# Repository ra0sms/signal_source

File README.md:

## Signal source for tuning receive antennas

More information - https://ra0sms.com/signal-source-for-bog/

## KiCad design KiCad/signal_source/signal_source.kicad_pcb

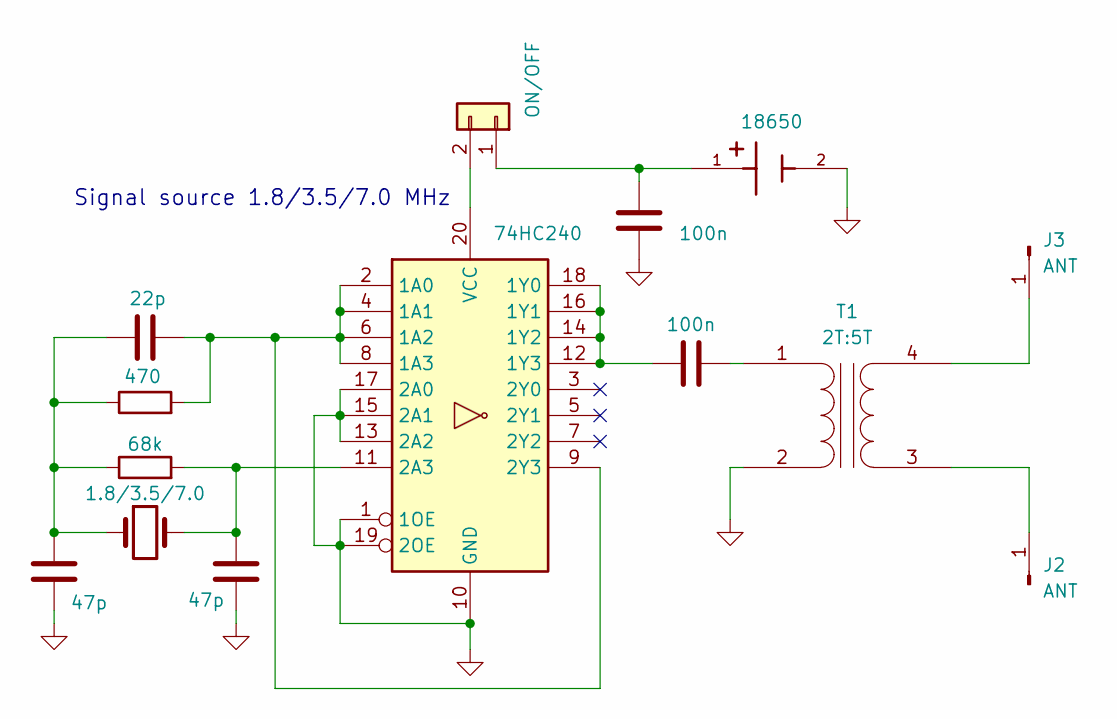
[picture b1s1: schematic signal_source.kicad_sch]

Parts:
BT2: 18650; BAT_BK-18650-PC2; PARTREV F
C1, C2: 100n; C_1206_3216Metric
C3: 22p; C_1206_3216Metric
C4, C5: 47p; C_1206_3216Metric
J1: ON/OFF; PinHeader_1x02_P2.54mm_Vertical
J2, J3: ANT; Banana_Jack_1Pin
R1: 68k; R_1206_3216Metric
R2: 470; R_1206_3216Metric
T1: 2T:5T; Transformer_BN73-202
U1: 74HC240; DIP-20_W7.62mm_Socket_LongPads
Y1: 1.8/3.5/7.0; Crystal_HC49-U_Vertical

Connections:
GND: BT2.2, C2.1, C4.1, C5.1, T1.2 (AB), U1.1 (1OE), U1.10 (GND), U1.13 (2A2), U1.15 (2A1), U1.17 (2A0), U1.19 (2OE); also elsewhere on the board
unnamed: C3.1, C4.2, R1.1, R2.1, Y1.1
unnamed: BT2.1, C2.2, J1.1
unnamed: J1.2, U1.20 (VCC)
unnamed 4: J2.1, T1.3 (SA); also elsewhere on the board
unnamed 5: J3.1, T1.4 (SB); also elsewhere on the board
unnamed 6: C1.2, T1.1 (AA); also elsewhere on the board
unnamed: C3.2, R2.2, U1.2 (1A0), U1.4 (1A1), U1.6 (1A2), U1.8 (1A3), U1.9 (2Y3)
unnamed: C1.1, U1.12 (1Y3), U1.14 (1Y2), U1.16 (1Y1), U1.18 (1Y0)
unnamed: C5.2, R1.2, U1.11 (2A3), Y1.2

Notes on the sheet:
Signal source 1.8/3.5/7.0 MHz

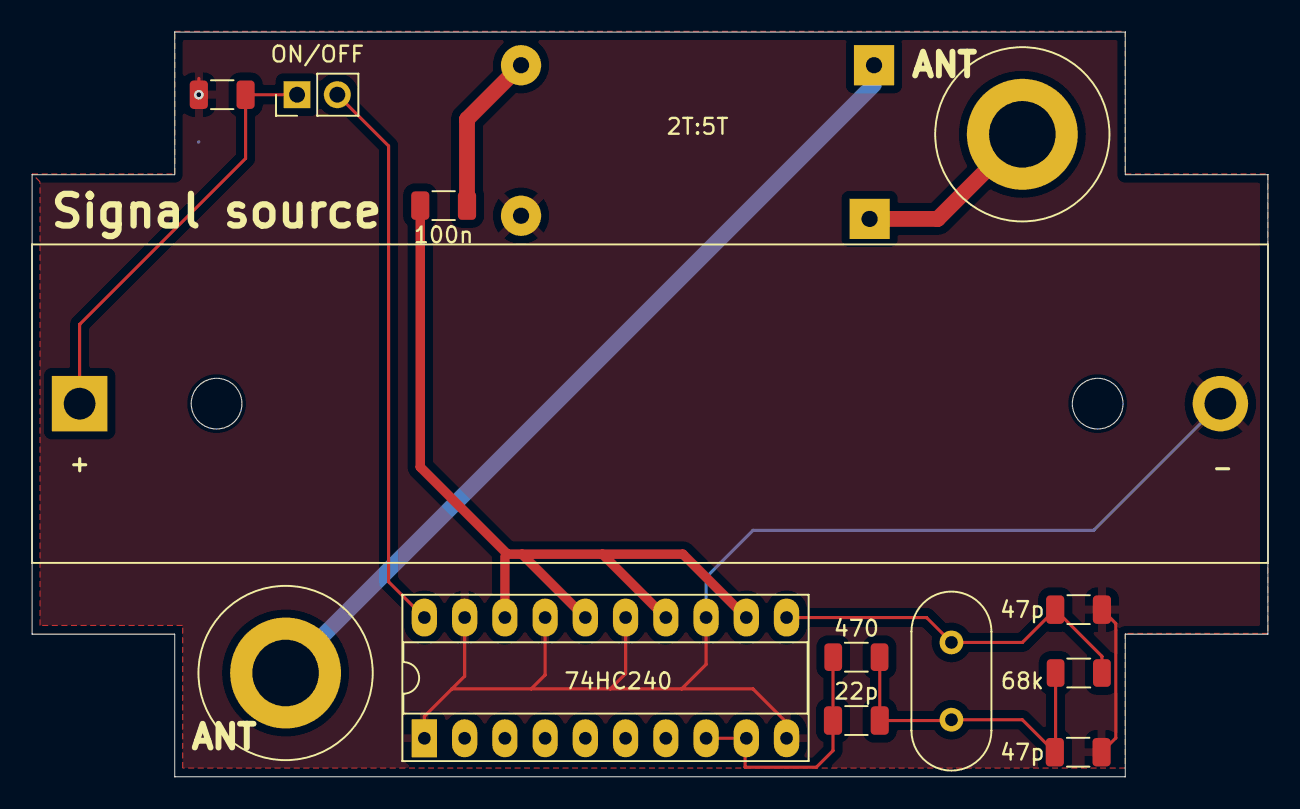
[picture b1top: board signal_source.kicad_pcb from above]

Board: 2 copper layers, 78.0 x 47.0 mm, 14 parts (0 on the bottom side), 10 nets.

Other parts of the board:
2T:5T: 2T:5T; Transformer_BN73-202

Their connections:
GND: 2T:5T.2 (AB); also elsewhere on the board
unnamed 4: 2T:5T.3 (SA); also elsewhere on the board
unnamed 5: 2T:5T.4 (SB); also elsewhere on the board
unnamed 6: 2T:5T.1 (AA); also elsewhere on the board

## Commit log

2024-12-20 add readme
